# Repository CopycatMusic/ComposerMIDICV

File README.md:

# Composer MIDICV

**A four-channel MIDI-to-CV/Gate Eurorack module, built around the RP2354A.**

Composer connects a DAW or MIDI instrument to analog synthesizers through USB MIDI or a 3.5 mm TRS MIDI input. Four CV outputs and four Gate outputs provide pitch, velocity, modulation, random voltages and clock signals across six hardware-selected modes.

[USER_MANUAL](docs/USER_MANUAL.md) · [Firmware guide](firmware/README.md) · [ManufacturingGuide](docs/ManufacturingGuide.md)

## Features

- USB MIDI input and TRS MIDI input
- Four unipolar CV outputs, with a firmware range of **0–8 V**
- Four nominal **0/5 V** Gate outputs
- Mono, dual-voice and four-voice MIDI modes, plus three dual-voice clock/transport modes.
- RGB note feedback, out-of-range indication and mode-change feedback.

## Specifications

| Parameter | Specification |
| --- | --- |
| Hardware revision | v1.0 |
| Format | 3U Eurorack, 4 HP |
| Front-panel dimensions | 20.3 × 128.5 mm |
| Mainboard dimensions | 20 × 110 mm |
| Power supply | +12 V via a 10-pin Eurorack header |
| Typical +12 V current draw | **20 mA** |
| Recommended +12 V supply allocation | **50 mA** |
| MIDI inputs | USB MIDI device and 3.5 mm TRS MIDI Type A |
| CV outputs | 4 channels, 0–8 V, unipolar |
| Pitch scaling | 1 V/oct; MIDI note 36 = 0 V |
| Pitch bend | ±2 semitones, fixed |
| Gate outputs | 4 channels, nominal 0/5 V |
| Trigger pulse width | 10 ms for note-on and clock triggers |
| DAC resolution | 12 bits per channel; two MCP4822 dual-channel DACs |
| Panel modes | 6 |
| Calibration | Per-channel two-point correction, saved to flash |

## Modes

Modes are selected by the two panel switches, not by changing the MIDI channel. MIDI channels select voices within the active mode.

| Mode | Name | CV1 / CV2 / CV3 / CV4 | Gate1 / Gate2 / Gate3 / Gate4 |
| --- | --- | --- | --- |
| 1 | `midi1` | Pitch / Velocity / CC1 / Random S&H | Gate / Gate / Note trigger / Note trigger |
| 2 | `midi2` | Voice 1 pitch / Velocity / Voice 2 pitch / Velocity | Voice 1 gate / Trigger / Voice 2 gate / Trigger |
| 3 | `midi3` | Voice 1 / 2 / 3 / 4 pitch | Voice 1 / 2 / 3 / 4 gate |
| 4 | `sequencer1` | Voice 1 pitch / Velocity / Voice 2 pitch / Velocity | Run / Reset / 1 PPQN / 8 PPQN |
| 5 | `sequencer2` | Voice 1 pitch / Velocity / Voice 2 pitch / Velocity | Run / Reset / 2 PPQN / 12 PPQN |
| 6 | `sequencer3` | Voice 1 pitch / Velocity / Voice 2 pitch / Velocity | Run / Reset / 4 PPQN / 24 PPQN |

In the dual-voice modes, MIDI channels **1–8** control Voice 1 and **9–16** control Voice 2. In `midi3`, the channel groups are **1–4**, **5–8**, **9–12** and **13–16**. Each group controls one voice; playing a chord on a single channel does not automatically distribute it across four outputs.

Pitch conversion uses **MIDI note 36 = 0 V**, with one octave per volt and a fixed pitch-bend range of approximately ±2 semitones. Velocity and CC1 map linearly from 0–127 to 0–8 V. The manual includes complete routing tables and patch examples.

## Quick start

1. With the rack powered off, connect the module's 10-pin power header in the correct orientation. v1.0 uses the rack's **+12 V** rail; USB-C provides the data connection and does not replace the module power supply.
2. Power the module and connect USB-C to a computer using a data cable, or connect a MIDI source to the **TRS Type A** input.
3. Select `midi1`. In your DAW, choose **Composer MIDICV / MIDICV MIDI** as the MIDI output destination; the exact displayed name depends on the host.
4. Patch **CV1** to a VCO's 1 V/oct input and **Gate1** to an envelope gate input. Send notes on MIDI channel 1, starting at note 36 or higher.
5. For modes 4–6, enable MIDI Clock and Start/Continue/Stop output to the module as well as MIDI notes.

See the [user manual](docs/USER_MANUAL.md) for power pin assignments, the mode selector, dual/four-voice patches, clock routing, flashing, calibration and troubleshooting.

## Design

The firmware is written in **C**, using **Raspberry Pi Pico SDK 2.2.0** and **TinyUSB**. USB packets and the UART MIDI stream are decoded into a common event format, then dispatched to the selected mode. The mode engine updates a shared output state; a 1 ms service loop handles switches, triggers, LEDs and output updates.

Two **MCP4822** dual-channel 12-bit DACs provide four CV channels through SPI frames generated by GPIO. An **OPA4991** analog stage scales the DAC outputs, while a **74AHCT244** buffer drives the DAC interface and Gate signals. The TRS input uses a **TLP2361** optocoupler. The mainboard and front panel are maintained as **KiCad 10** projects.

The firmware separates hardware drivers, MIDI parsing/routing, musical modes, pitch/calibration and UI feedback. The six default modes are defined in [mode_config.c](firmware/src/config/mode_config.c).

## Build and flash

Install **CMake 3.22+**, **Ninja**, **Python 3** and an **Arm GNU embedded toolchain** with newlib and `nosys.specs`. The local build uses Arm GNU **14.2.Rel1**. Put `arm-none-eabi-gcc` and the accompanying tools on `PATH`.

From the project root, initialize the SDK dependency:

```sh
git submodule update --init --recursive third_party/pico-sdk
```

macOS / Linux:

```sh
export PICO_SDK_PATH="$PWD/third_party/pico-sdk"
cmake -S firmware -B firmware/build-arm -G Ninja \
  -DPICO_PLATFORM=rp2350-arm-s -DPICO_BOARD=pico2 \
  -DCMAKE_BUILD_TYPE=Release
cmake --build firmware/build-arm --parallel
```

Windows PowerShell:

```powershell
$env:PICO_SDK_PATH = Join-Path $PWD "third_party/pico-sdk"
cmake -S firmware -B firmware/build-arm -G Ninja -DPICO_PLATFORM=rp2350-arm-s -DPICO_BOARD=pico2 -DCMAKE_BUILD_TYPE=Release
cmake --build firmware/build-arm --parallel
```

The build produces `firmware/build-arm/composer_midicv.uf2` and copies it to `firmware/dist/composer_midicv.uf2`. `pico2` supplies the SDK build configuration for the custom RP2354A board; the module's pin mapping is defined in the firmware.

With module power available, enter USB boot mode by holding **BOOTSEL** while resetting the board with **RUN**. Connect USB and copy the UF2 to the mounted RP2350 boot drive, then allow the board to reboot. See the [flashing instructions](docs/USER_MANUAL.md#6-固件构建与刷写) for the full sequence.

## Hardware and manufacturing files

Use the **v1.0** mainboard files together with the current panel files:

| Resource | Location |
| --- | --- |
| Mainboard KiCad project | [ComposerMIDICV.kicad_pro](hardware/ComposerMIDICV/ComposerMIDICV.kicad_pro) |
| Mainboard schematic | [ComposerMIDICV.kicad_sch](hardware/ComposerMIDICV/ComposerMIDICV.kicad_sch) |
| Mainboard PCB | [ComposerMIDICV.kicad_pcb](hardware/ComposerMIDICV/ComposerMIDICV.kicad_pcb) |
| v1.0 production BOM | [COMPOSERv1.0_bom.csv](hardware/ComposerMIDICV/production/COMPOSERv1.0_bom.csv) |
| v1.0 Gerber and drill files | [COMPOSERv1.0Gerber.zip](hardware/ComposerMIDICV/production/COMPOSERv1.0Gerber.zip) |
| v1.0 pick-and-place coordinates | [COMPOSERv1.0_positions.csv](hardware/ComposerMIDICV/production/COMPOSERv1.0_positions.csv) |
| Front-panel KiCad project | [ComposerPanel.kicad_pro](hardware/ComposerPanel/ComposerPanel.kicad_pro) |
| Front-panel manufacturing files | [ComposerPanel.zip](hardware/ComposerPanel/production/ComposerPanel.zip) |
| Front-panel artwork | [Panel silkscreen SVG](hardware/ComposerPanel/design/Composer_MIDI_CV_Panel_Silkscreen.svg) |
| Earlier revisions | [hardware/legacy](hardware/legacy/) |

Use the **v1.0 production BOM** linked above for the current revision. Some BOM entries require separate sourcing, including the jacks and RP2354A; the L3 supplier field contains a manufacturer part number rather than an LCSC `C...` identifier.

The symbols and custom footprints used in v1.0 are included as project-local snapshots. Install the standard KiCad 10 libraries; optional 3D models still use external library variables. See the [manufacturing guide](docs/ManufacturingGuide.md) for file selection and library details.

## License

The author's original source and design files use **AGPL-3.0-only**; see [LICENSE](LICENSE). Third-party material retains its own licence; see [THIRD_PARTY_NOTICES.md](THIRD_PARTY_NOTICES.md).

## Contact

Email: [tg3299182383@gmail.com](mailto:tg3299182383@gmail.com)

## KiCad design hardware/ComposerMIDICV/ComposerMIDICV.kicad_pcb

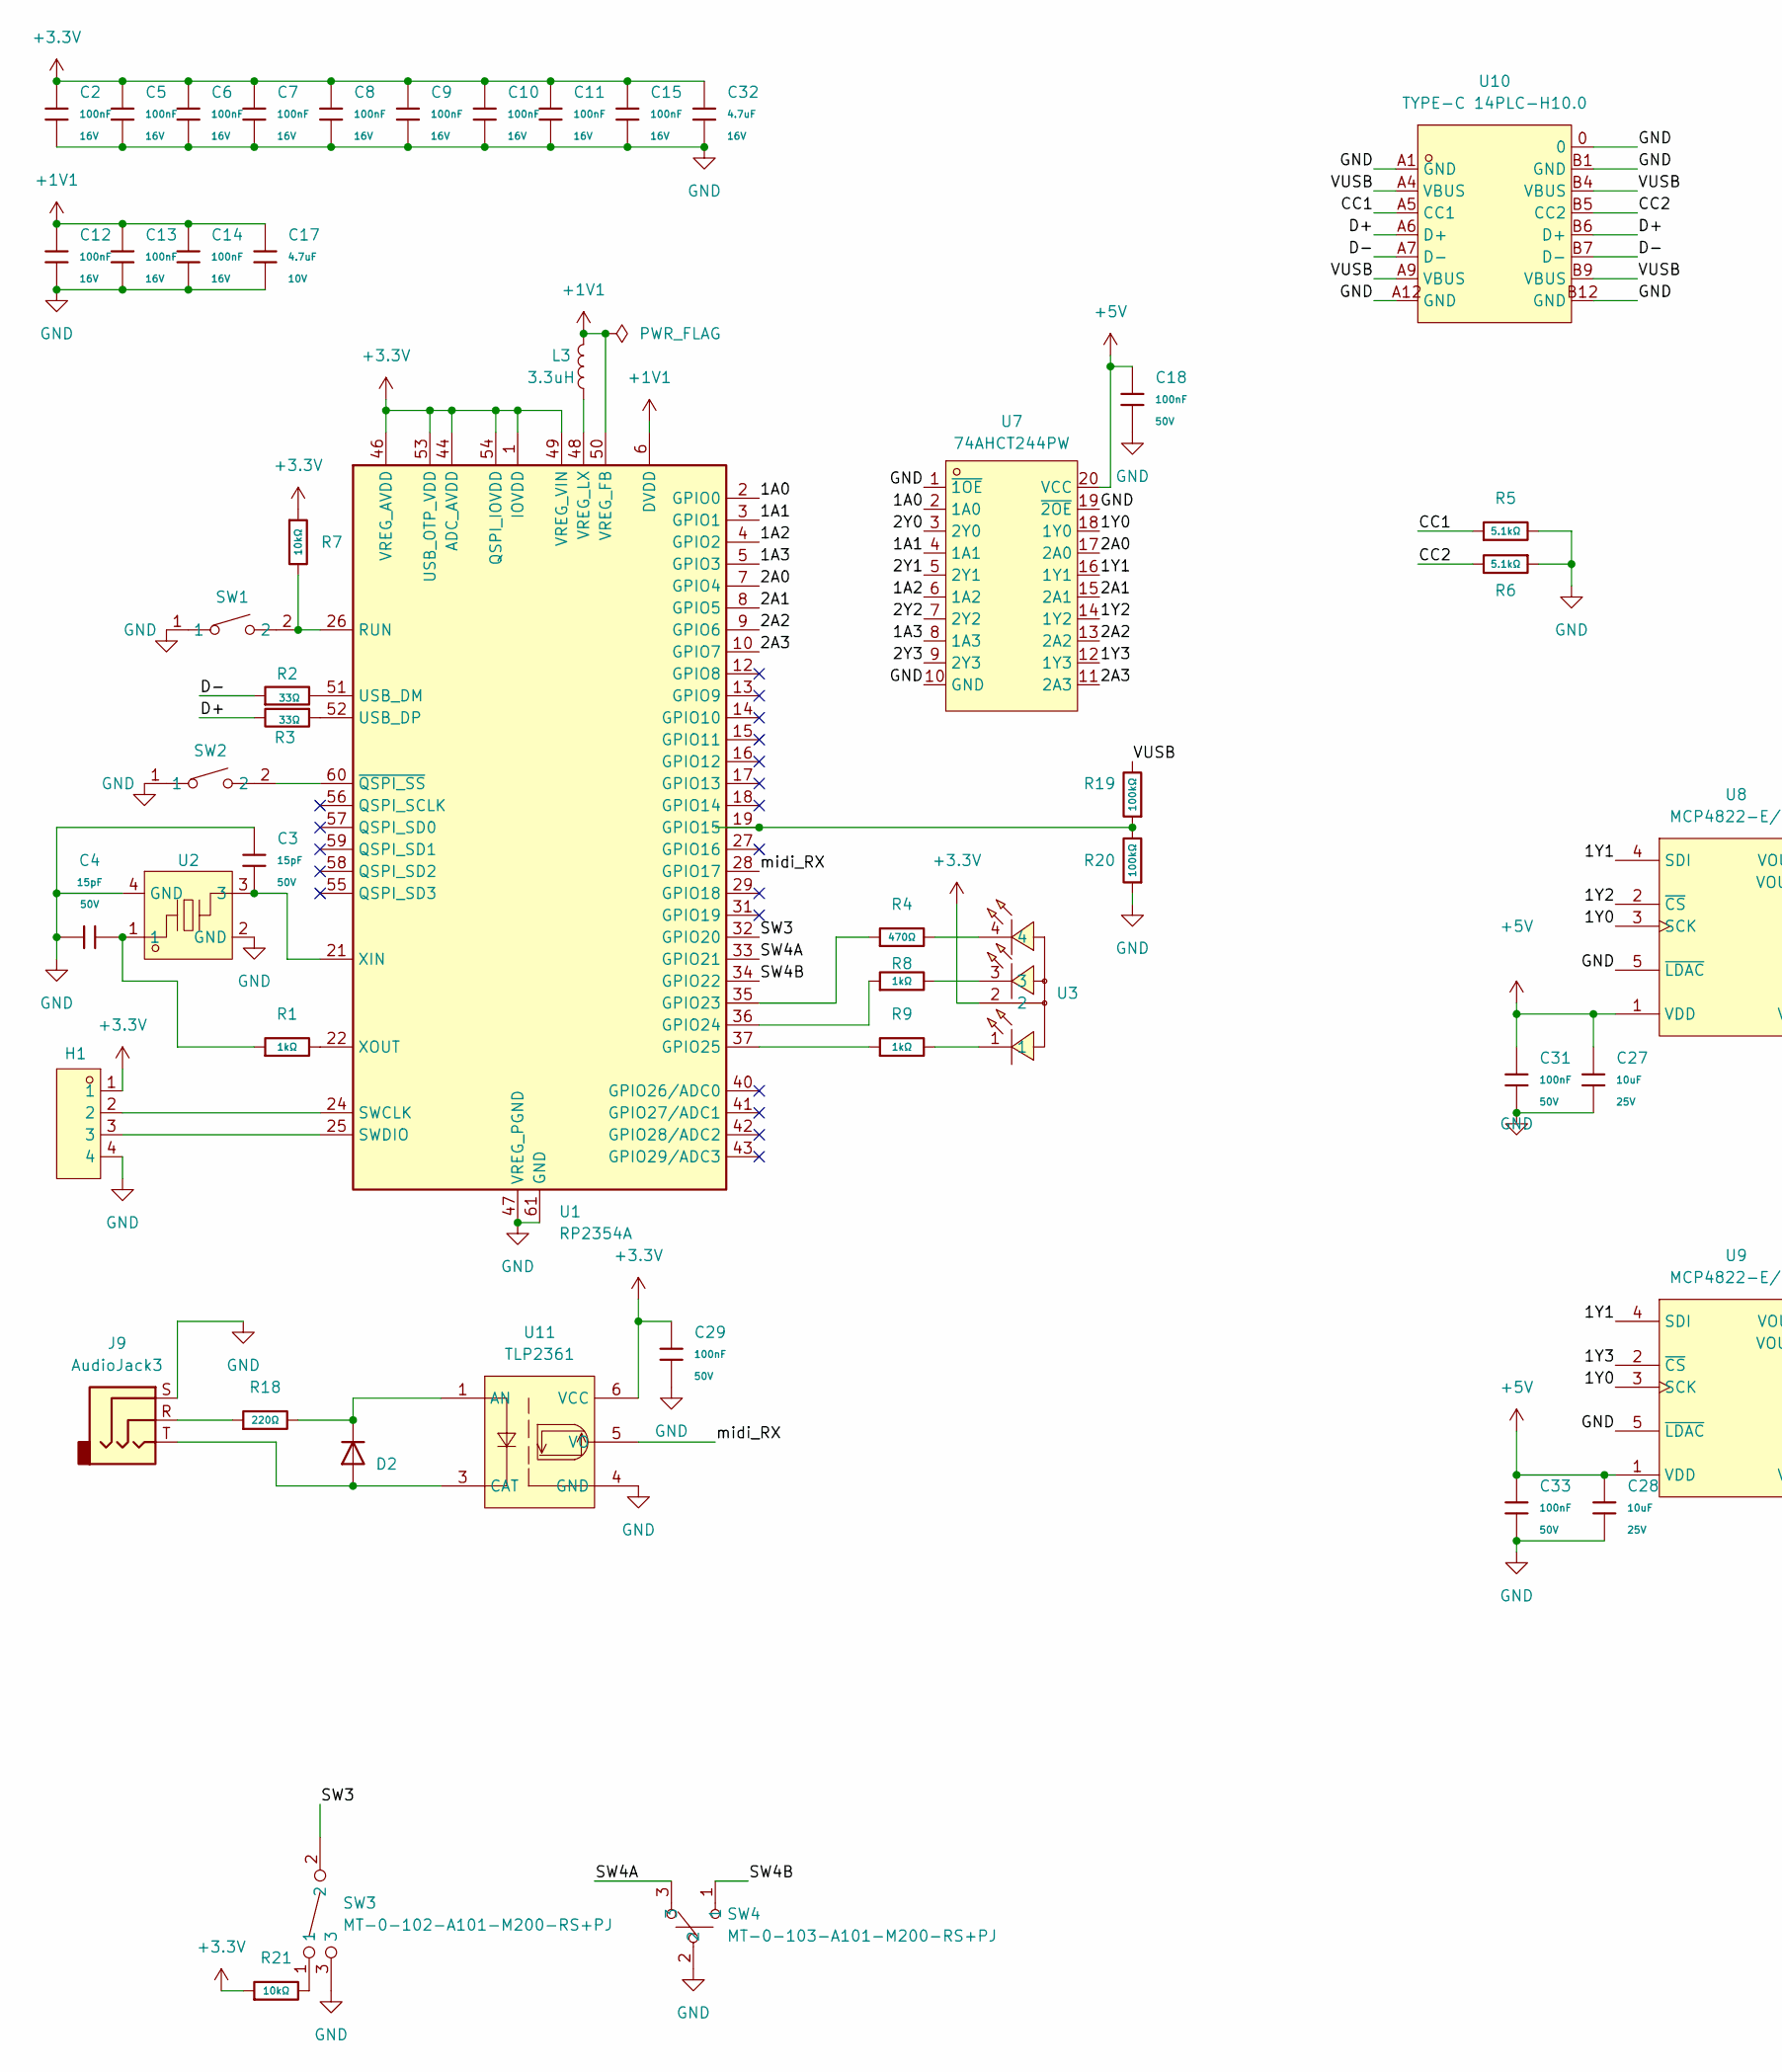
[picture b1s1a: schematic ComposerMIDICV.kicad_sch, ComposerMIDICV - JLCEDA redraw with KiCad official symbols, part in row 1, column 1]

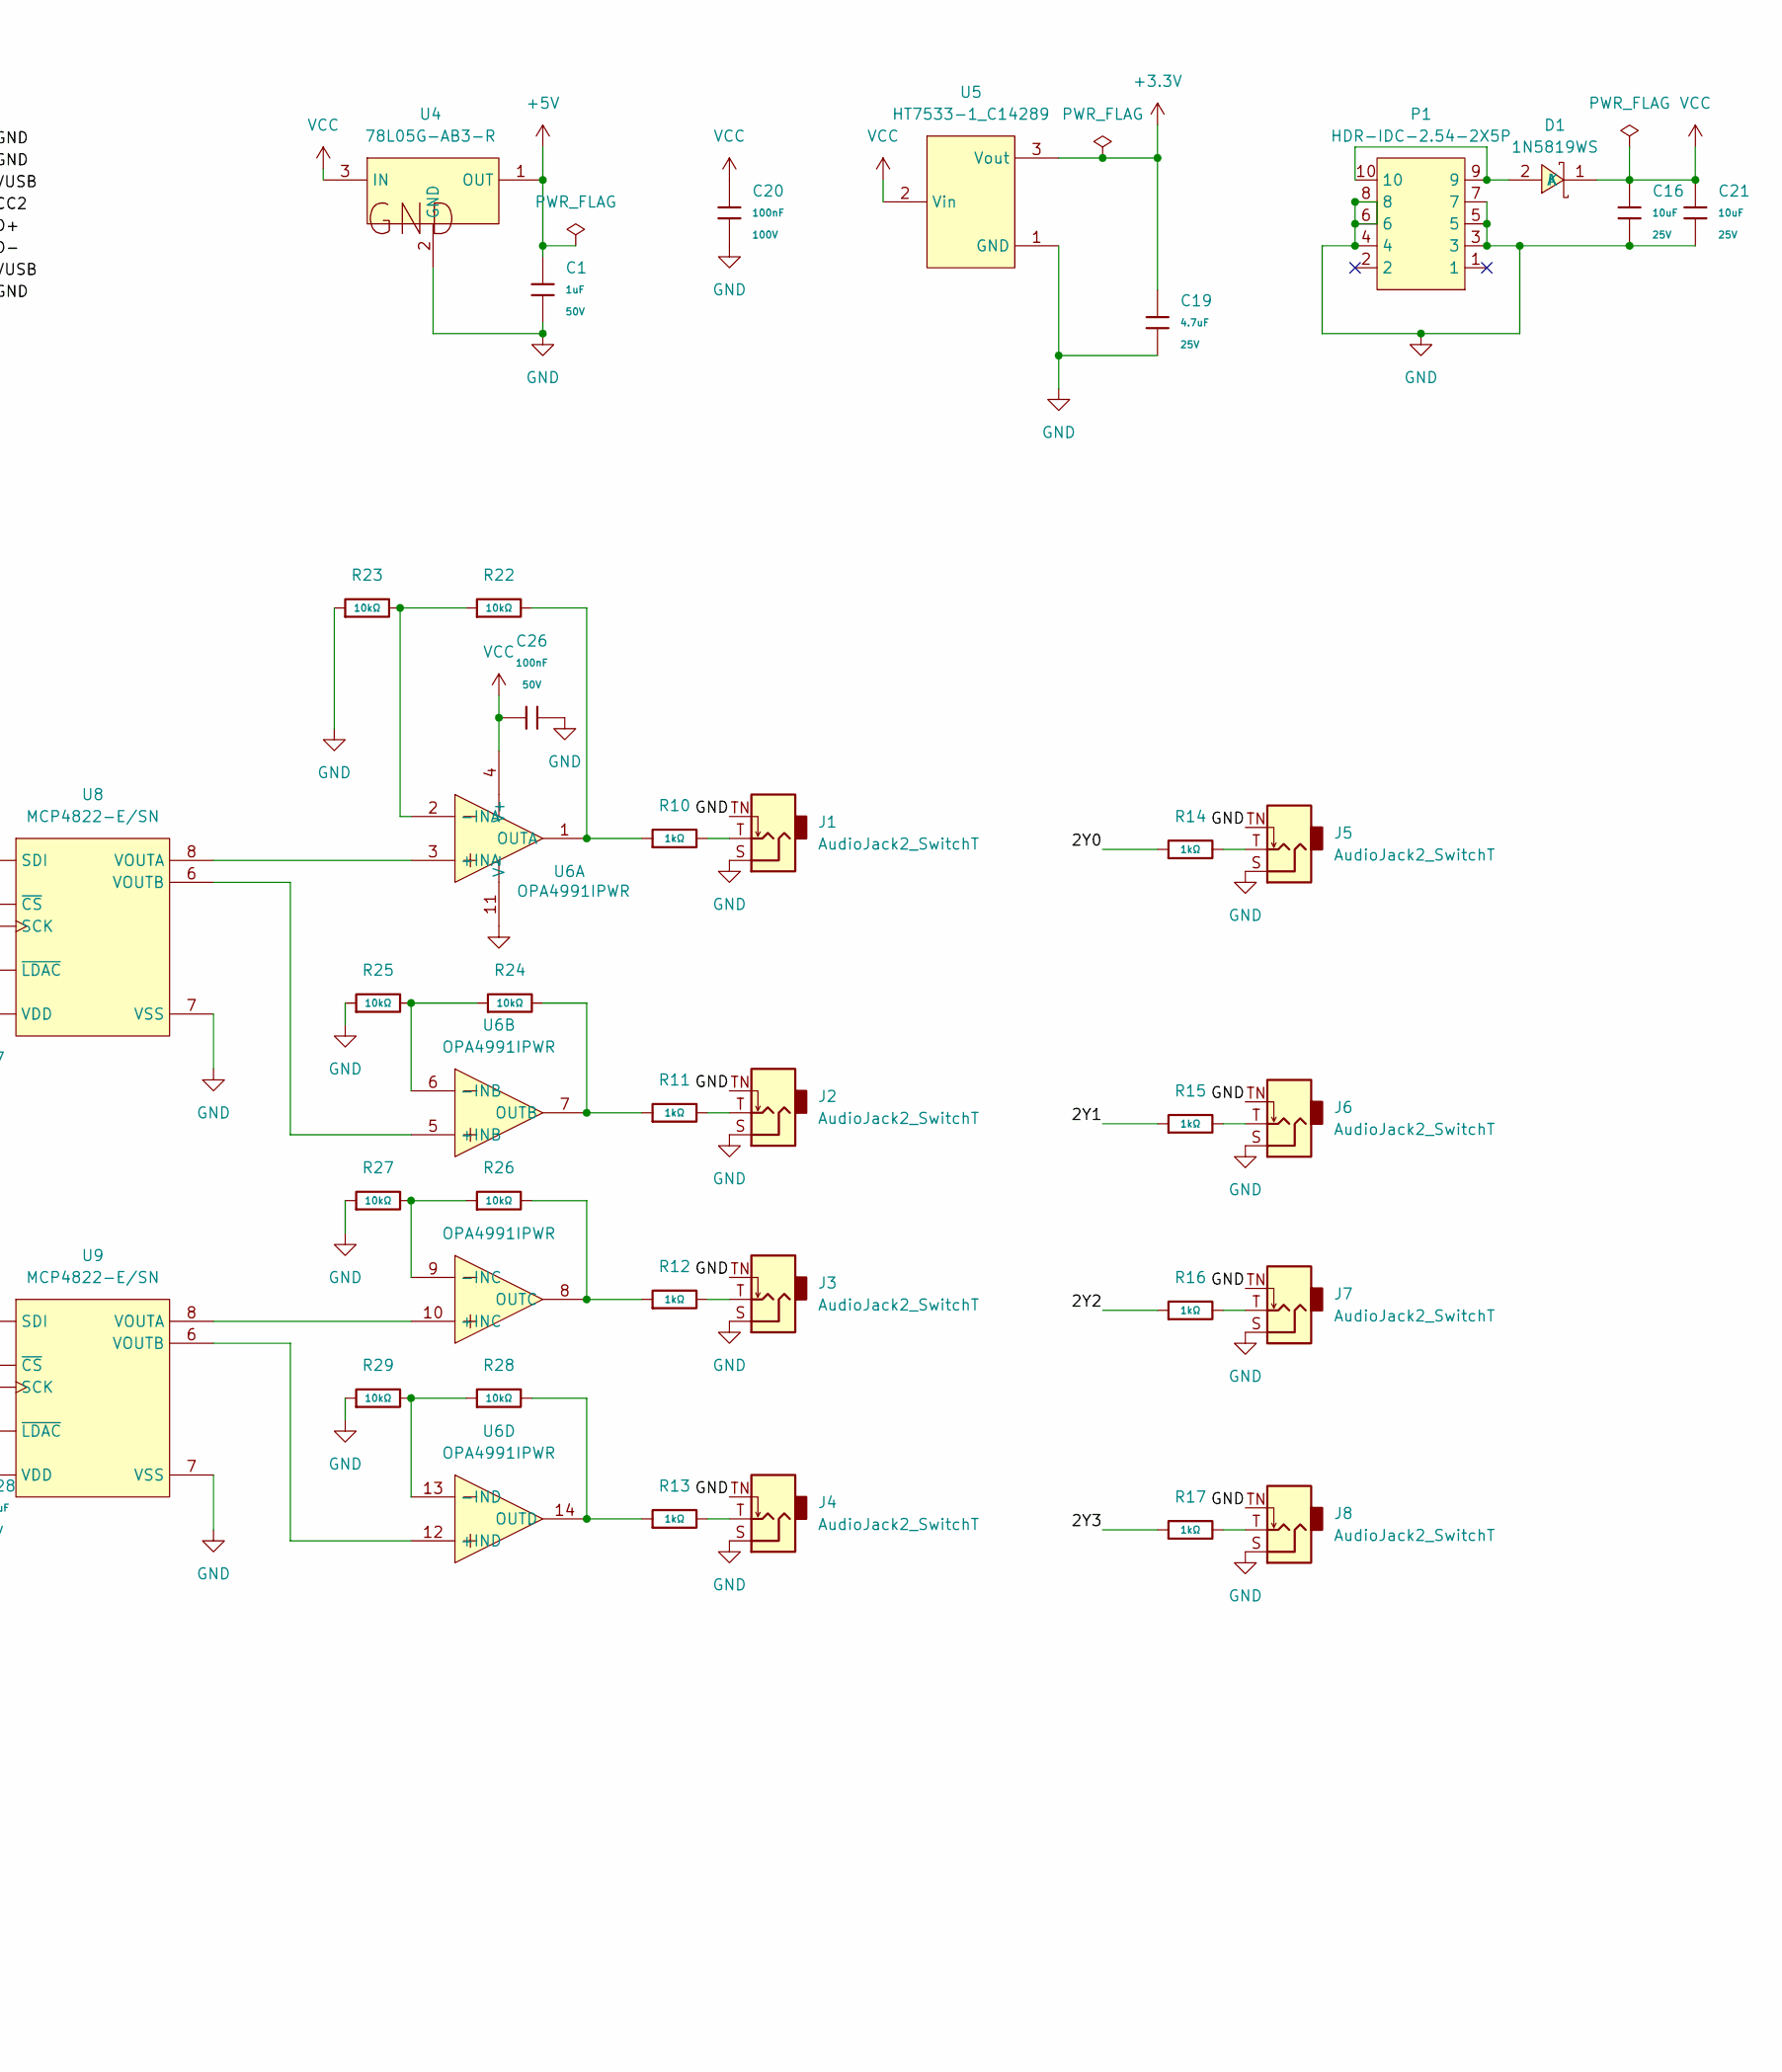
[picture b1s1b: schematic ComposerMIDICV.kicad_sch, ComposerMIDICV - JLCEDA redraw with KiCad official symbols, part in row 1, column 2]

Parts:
C1: 1uF; C_0805; Voltage Rated 50V; Tolerance ±10%; Part CL21B105KBFNNNE; LCSC C28323
C2, C5, C6, C7, C8, C9, C10, C11, C12, C13, C14, C15: 100nF; C_0402; Voltage Rated 16V; Tolerance ±10%; Part CL05B104KO5NNNC; LCSC C1525
C3, C4: 15pF; C_0402; Voltage Rated 50V; Tolerance ±5%; Part 0402CG150J500NT; LCSC C1548
C16, C21: 10uF; C_0805; Voltage Rated 25V; Tolerance ±10%; Part CL21A106KAYNNNE; LCSC C15850
C17: 4.7uF; C_0402; Voltage Rated 10V; Tolerance ±20%; Part CL05A475MP5NRNC; LCSC C23733
C18, C26, C29, C31, C33: 100nF; C_0603; Voltage Rated 50V; Tolerance ±10%; Part CC0603KRX7R9BB104; LCSC C14663
C19: 4.7uF; C_0805; Voltage Rated 25V; Tolerance ±10%; Part CL21A475KAQNNNE; LCSC C1779
C20: 100nF; C_0805; Voltage Rated 100V; Tolerance ±10%; Part CL21B104KCFNNNE; LCSC C28233
C27, C28: 10uF; C_0603; Voltage Rated 25V; Tolerance ±20%; Part CL10A106MA8NRNC; LCSC C96446
C32: 4.7uF; C_0603; Voltage Rated 16V; Tolerance ±10%; Part CL10A475KO8NNNC; LCSC C19666
D1: 1N5819WS; SOD-323_L1.8-W1.3-LS2.5-RD; MPN 1N5819WS; LCSC Part C191023
D2: 1N4148WS; D_SOD-323; Forward Voltage (Vf@If) 1.25V@150mA; Reverse Voltage (Vr) 100V; Part 1N4148WS; LCSC C2128
H1: PH2.54-01-04PZD; HDR-TH_4P-P2.54-V-M-1; MPN PH2.54-01-04PZD; LCSC Part C7501582
J1, J2, J3, J4, J5, J6, J7, J8: AudioJack2_SwitchT; Jack_3.5mm_QingPu_WQP-PJ301M-12_Vertical
J9: AudioJack3; Jack_3.5mm_QingPu_WQP-PJ366ST_Vertical
L3: 3.3uH; R_0805_2012Metric; MPN AOTA-B201610S3R3-101-T
P1: HDR-IDC-2.54-2X5P; IDC-TH_10P-P2.54_C5665; MPN 2.54-2*5P简牛; LCSC Part C5665
R1: 1kΩ; R_0402; Overload Voltage (Max) 50V; Tolerance ±1%; Part 0402WGF1001TCE; LCSC C11702
R2, R3: 33Ω; R_0402; Overload Voltage (Max) 50V; Tolerance ±1%; Part 0402WGF330JTCE; LCSC C25105
R4: 470Ω; R_0603; Overload Voltage (Max) 75V; Tolerance ±1%; Part 0603WAF4700T5E; LCSC C23179
R5, R6: 5.1kΩ; R_0603; Overload Voltage (Max) 75V; Tolerance ±1%; Part 0603WAF5101T5E; LCSC C23186
R7, R21, R22, R23, R24, R25, R26, R27, R28, R29: 10kΩ; R_0603; Overload Voltage (Max) 75V; Tolerance ±1%; Part 0603WAF1002T5E; LCSC C25804
R8, R9, R10, R11, R12, R13, R14, R15, R16, R17: 1kΩ; R_0603; Overload Voltage (Max) 75V; Tolerance ±1%; Part 0603WAF1001T5E; LCSC C21190
R18: 220Ω; R_0603; Overload Voltage (Max) 75V; Tolerance ±1%; Part 0603WAF2200T5E; LCSC C22962
R19, R20: 100kΩ; R_0402; Overload Voltage (Max) 50V; Tolerance ±1%; Part 0402WGF1003TCE; LCSC C25741
SW1, SW2: TS-1088-AR02016; SW-SMD_L3.9-W3.0-P4.45; MPN TS-1088-AR02016; LCSC Part C720477
SW3: MT-0-102-A101-M200-RS+PJ; SW-TH_MT-0-103-A101-M200-RS; MPN MT-0-102-A101-M200-RS; LCSC Part C1788492
SW4: MT-0-103-A101-M200-RS+PJ; SW-TH_MT-0-103-A101-M200-RS; MPN MT-0-103-A101-M200-RS; LCSC Part C1788493
U1: RP2354A; QFN-60-1EP_7x7mm_P0.4mm_EP3.4x3.4mm
U2: ABM8-272-T3_C20625731; CRYSTAL-SMD_4P-L3.2-W2.5-BL; MPN ABM8-272-T3; LCSC Part C20625731
U3: TJ-L5FPTXHMCYLCRGB-A5; LED-TH_4P-BD5.8-P1.30; MPN TJ-L5FPTXHMCYLCRGB-A5; LCSC Part C20613339
U4: 78L05G-AB3-R; SOT-89-3_L4.5-W2.5-P1.50-LS4.2-BR; MPN 78L05G-AB3-R; LCSC Part C71136
U5: HT7533-1_C14289; SOT-89-3_L4.5-W2.5-P1.50-LS4.2-BR; MPN HT7533-1; LCSC Part C14289
U6: OPA4991IPWR; TSSOP-14_L5.0-W4.4-P0.65-LS6.4-BL; MPN OPA4991IPWR; LCSC Part C2873620
U7: 74AHCT244PW; TSSOP-20_L6.5-W4.4-P0.65-LS6.4-BL; MPN 74AHCT244PW; LCSC Part C54815894
U8, U9: MCP4822-E/SN; SOIC-8_L4.9-W3.9-P1.27-LS6.0-BL; MPN MCP4822-E/SN; LCSC Part C16040
U10: TYPE-C 14PLC-H10.0; USB-C-TH_SHOUHAN_TYPE-C-14PLC-H10.0; MPN TYPE-C 14PLC-H10.0; LCSC Part C3151746
U11: TLP2361; OPTO-SMD-5_L3.7-W4.6-P1.27-LS7.0-BR; MPN TLP2361(TPL,E; LCSC Part C107626

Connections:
+1V1: C12.1, C13.1, C14.1, C17.1, L3.2, U1.6 (DVDD), U1.23 (DVDD), U1.39 (DVDD), U1.50 (VREG_FB)
+3.3V: C2.1, C5.1, C6.1, C7.1, C8.1, C9.1, C10.1, C11.1, C15.1, C19.1, C29.1, C32.1, H1.1, R7.1, R21.1, U1.1 (IOVDD), U1.11 (IOVDD), U1.20 (IOVDD), U1.30 (IOVDD), U1.38 (IOVDD), U1.44 (ADC_AVDD), U1.45 (IOVDD), U1.46 (VREG_AVDD), U1.49 (VREG_VIN), U1.53 (USB_OTP_VDD), U1.54 (QSPI_IOVDD), U3.2, U5.3 (Vout), U11.6 (VCC)
+5V: C1.1, C18.1, C27.1, C28.1, C31.1, C33.1, U4.1 (OUT), U7.20 (VCC), U8.1 (VDD), U9.1 (VDD)
/1A0: U1.2 (GPIO0), U7.2 (1A0)
/1A1: U1.3 (GPIO1), U7.4 (1A1)
/1A2: U1.4 (GPIO2), U7.6 (1A2)
/1A3: U1.5 (GPIO3), U7.8 (1A3)
/1Y0: U7.18 (1Y0), U8.3 (SCK), U9.3 (SCK)
/1Y1: U7.16 (1Y1), U8.4 (SDI), U9.4 (SDI)
/1Y2: U7.14 (1Y2), U8.2 (~CS)
/1Y3: U7.12 (1Y3), U9.2 (~CS)
/2A0: U1.7 (GPIO4), U7.17 (2A0)
/2A1: U1.8 (GPIO5), U7.15 (2A1)
/2A2: U1.9 (GPIO6), U7.13 (2A2)
/2A3: U1.10 (GPIO7), U7.11 (2A3)
/2Y0: R14.1, U7.3 (2Y0)
/2Y1: R15.1, U7.5 (2Y1)
/2Y2: R16.1, U7.7 (2Y2)
/2Y3: R17.1, U7.9 (2Y3)
/CC1: R5.1, U10.A5 (CC1)
/CC2: R6.2, U10.B5 (CC2)
/D+: R3.2, U10.A6 (D+), U10.B6 (D+)
/D-: R2.1, U10.A7 (D-), U10.B7 (D-)
/SW3: SW3.2, U1.32 (GPIO20)
/SW4A: SW4.3, U1.33 (GPIO21)
/SW4B: SW4.1, U1.34 (GPIO22)
/VUSB: R19.2, U10.A4 (VBUS), U10.A9 (VBUS), U10.B4 (VBUS), U10.B9 (VBUS)
/midi_RX: U1.28 (GPIO17), U11.5 (VO)
GND: C1.2, C2.2, C3.1, C4.1, C5.2, C6.2, C7.2, C8.2, C9.2, C10.2, C11.2, C12.2, C13.2, C14.2, C15.2, C16.2, C17.2, C18.2, C19.2, C20.2, C21.2, C26.2, C27.2, C28.2, C29.2, C31.2, C32.2, C33.2, H1.4, J1.S, J1.TN, J2.S, J2.TN, J3.S, J3.TN, J4.S, J4.TN, J5.S, J5.TN, J6.S, J6.TN, J7.S, J7.TN, J8.S, J8.TN, J9.S, P1.3, P1.4, P1.5, P1.6, P1.7, P1.8, R5.2, R6.1, R20.1, R23.1, R25.1, R27.1, R29.1, SW1.1, SW2.1, SW3.3, SW4.2, U1.47 (VREG_PGND), U1.61 (GND), U2.2 (GND), U2.4 (GND), U4.2 (GND), U5.1 (GND), U6.11 (V-), U7.1 (~1OE), U7.10 (GND), U7.19 (~2OE), U8.5 (~LDAC), U8.7 (VSS), U9.5 (~LDAC), U9.7 (VSS), U10.0, U10.A1 (GND), U10.A12 (GND), U10.B1 (GND), U10.B12 (GND), U11.4 (GND)
unnamed: C4.2, R1.1, U2.1
unnamed: D1.2 (A), P1.9, P1.10
unnamed: J1.T, R10.2
unnamed: J2.T, R11.2
unnamed: J3.T, R12.2
unnamed: J4.T, R13.2
unnamed: J5.T, R14.2
unnamed: J6.T, R15.2
unnamed: J7.T, R16.2
unnamed: J8.T, R17.2
unnamed: J9.R, R18.1
unnamed: R4.2, U3.4
unnamed: R8.2, U3.3
unnamed: R9.2, U3.1
unnamed: R21.2, SW3.1
unnamed: R19.1, R20.2, U1.19 (GPIO15)
unnamed: R4.1, U1.35 (GPIO23)
unnamed: R8.1, U1.36 (GPIO24)
unnamed: R9.1, U1.37 (GPIO25)
unnamed: R7.2, SW1.2, U1.26 (RUN)
unnamed: H1.2, U1.24 (SWCLK)
unnamed: H1.3, U1.25 (SWDIO)
unnamed: R2.2, U1.51 (USB_DM)
unnamed: R3.1, U1.52 (USB_DP)
unnamed: L3.1, U1.48 (VREG_LX)
unnamed: C3.2, U1.21 (XIN), U2.3
unnamed: R1.2, U1.22 (XOUT)
unnamed: SW2.2, U1.60 (~QSPI_SS)
unnamed: U6.3 (+INA), U8.8 (VOUTA)
unnamed: R22.1, R23.2, U6.2 (-INA)
unnamed: R10.1, R22.2, U6.1 (OUTA)
unnamed: U6.5 (+INB), U8.6 (VOUTB)
unnamed: R24.1, R25.2, U6.6 (-INB)
unnamed: R11.1, R24.2, U6.7 (OUTB)
unnamed: U6.10 (+INC), U9.8 (VOUTA)
unnamed: R26.1, R27.2, U6.9 (-INC)
unnamed: R12.1, R26.2, U6.8 (OUTC)
unnamed: U6.12 (+IND), U9.6 (VOUTB)
unnamed: R28.1, R29.2, U6.13 (-IND)
unnamed: R13.1, R28.2, U6.14 (OUTD)
unnamed: D2.1, R18.2, U11.1 (AN)
unnamed: D2.2, J9.T, U11.3 (CAT)
VCC: C16.1, C20.1, C21.1, C26.1, D1.1 (K), U4.3 (IN), U5.2 (Vin), U6.4 (V+)

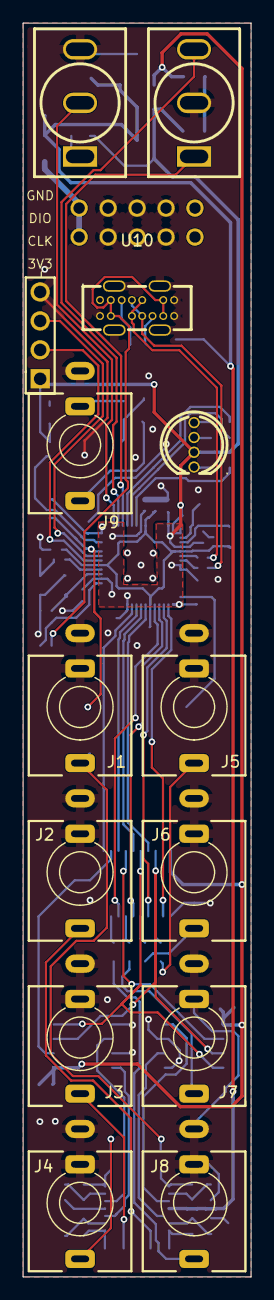
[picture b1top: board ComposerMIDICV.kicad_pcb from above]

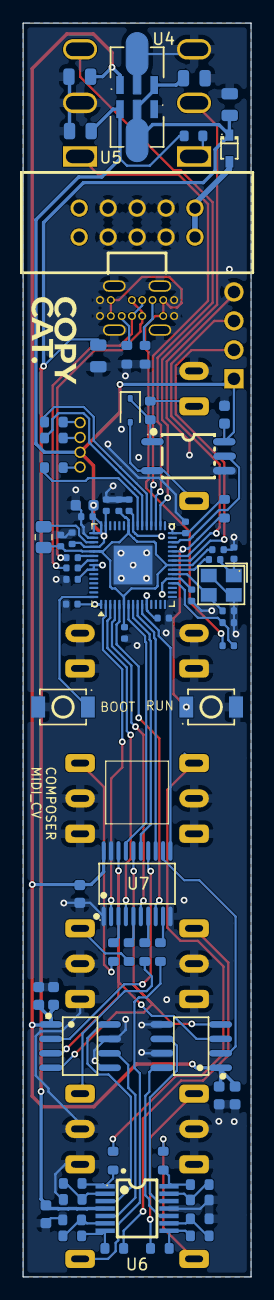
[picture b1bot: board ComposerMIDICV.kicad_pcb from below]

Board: 2 copper layers, 20.0 x 110.0 mm, 86 parts (72 on the bottom side), 72 nets.

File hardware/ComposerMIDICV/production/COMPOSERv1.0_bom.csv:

Designator,Footprint,Quantity,Value,LCSC Part #
C1,C_0805,1,1uF,C28323
"C10, C11, C12, C13, C14, C15, C2, C5, C6, C7, C8, C9",C_0402,12,100nF,C1525
"C16, C21",C_0805,2,10uF,C15850
C17,C_0402,1,4.7uF,C23733
"C18, C26, C29, C31, C33",C_0603,5,100nF,C14663
C19,C_0805,1,4.7uF,C1779
C20,C_0805,1,100nF,C28233
"C27, C28",C_0603,2,10uF,C96446
"C3, C4",C_0402,2,15pF,C1548
C32,C_0603,1,4.7uF,C19666
D1,SOD-323_L1.8-W1.3-LS2.5-RD,1,1N5819WS,C191023
D2,D_SOD-323,1,1N4148WS,C2128
H1,HDR-TH_4P-P2.54-V-M-1,1,PH2.54-01-04PZD,C7501582
"J1, J2, J3, J4, J5, J6, J7, J8",Jack_3.5mm_QingPu_WQP-PJ301M-12_Vertical,8,AudioJack2_SwitchT,
J9,Jack_3.5mm_QingPu_WQP-PJ366ST_Vertical,1,AudioJack3,
L3,0805,1,3.3uH,AOTA-B201610S3R3-101-T 
P1,IDC-TH_10P-P2.54_C5665,1,HDR-IDC-2.54-2X5P,C5665
R1,R_0402,1,1kΩ,C11702
"R10, R11, R12, R13, R14, R15, R16, R17, R8, R9",R_0603,10,1kΩ,C21190
R18,R_0603,1,220Ω,C22962
"R19, R20",R_0402,2,100kΩ,C25741
"R2, R3",R_0402,2,33Ω,C25105
"R21, R22, R23, R24, R25, R26, R27, R28, R29, R7",R_0603,10,10kΩ,C25804
R4,R_0603,1,470Ω,C23179
"R5, R6",R_0603,2,5.1kΩ,C23186
"SW1, SW2",SW-SMD_L3.9-W3.0-P4.45,2,TS-1088-AR02016,C720477
SW3,SW-TH_MT-0-103-A101-M200-RS,1,MT-0-102-A101-M200-RS+PJ,C1788492
SW4,SW-TH_MT-0-103-A101-M200-RS,1,MT-0-103-A101-M200-RS+PJ,C1788493
U1,QFN-60-1EP_7x7mm_P0.4mm_EP3.4x3.4mm,1,RP2354A,
U10,USB-C-TH_SHOUHAN_TYPE-C-14PLC-H10.0,1,TYPE-C 14PLC-H10.0,C3151746
U11,OPTO-SMD-5_L3.7-W4.6-P1.27-LS7.0-BR,1,TLP2361,C107626
U2,CRYSTAL-SMD_4P-L3.2-W2.5-BL,1,ABM8-272-T3_C20625731,C20625731
U3,LED-TH_4P-BD5.8-P1.30,1,TJ-L5FPTXHMCYLCRGB-A5,C20613339
U4,SOT-89-3_L4.5-W2.5-P1.50-LS4.2-BR,1,78L05G-AB3-R,C71136
U5,SOT-89-3_L4.5-W2.5-P1.50-LS4.2-BR,1,HT7533-1_C14289,C14289
U6,TSSOP-14_L5.0-W4.4-P0.65-LS6.4-BL,1,OPA4991IPWR,C2873620
U7,TSSOP-20_L6.5-W4.4-P0.65-LS6.4-BL,1,74AHCT244PW,C54815894
"U8, U9",SOIC-8_L4.9-W3.9-P1.27-LS6.0-BL,2,MCP4822-E/SN,C16040
